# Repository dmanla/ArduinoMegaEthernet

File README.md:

# Arduino-Mega Compatible Secure Connectivity Development Platform

**WARNING**: This project is under development and has not yet been validated.

This is an open hardware platform designed for the development of secure wired-network applications. It is fully compatible with all Arduino Mega-compatible hardware and software.

This project was inspired by (but not a copy of) the Freetronics EtherMega: https://github.com/freetronics/EtherMega
This project was created as an alternative to the platform offered by Freetronics.

Features:
- CH340 USB->Serial Converter (Functionally similar to FT232, Driver should be installed automatically)
- Jumper Configurable IO: Certain pins (D3, D6, D8, D9, D13) can be connected to the headers or to integrated peripheral pins.
- 5V 2A USB-C Input
- 6V - 32V VIN Input 
- MicroSD Card Slot
- 10/100 Ethernet provided over SPI using the W5500
- SE050 EdgeLock Plug and Trust Secure Element to provide security features for connected applications, accessible using I2C
- ISM330DHCX Inertial Measurement Unit, accessible using I2C
- MCP7940N Real Time Clock, accessible using I2C
- Level Shifted I2C: Provides connection points for 3V3 I2C Devices (Extra Header), and 5V I2C Devices (Standard Mega Headers)

## Top Render

## Bottom Render

## Side Render

## Relevant Datasheets

- [CH340N](https://datasheet.lcsc.com/szlcsc/Jiangsu-Qin-Heng-CH340C_C84681.pdf): USB->Serial Bridge
- [AP22805AW5](https://www.diodes.com/assets/Datasheets/AP22804_14.pdf): USB Protection
- [AP63205](https://www.diodes.com/assets/Datasheets/AP63200-AP63201-AP63203-AP63205.pdf): DC-DC Switching Converters
- [W5500](http://wizwiki.net/wiki/lib/exe/fetch.php/products:w5500:w5500_ds_v109e.pdf): SPI->Ethernet Bridge
- [ISM330DHCX](https://www.st.com/resource/en/datasheet/ism330dhcx.pdf): "AI Enabled" Inertial Measurement Unit
- [SE050C2HQ1](https://www.nxp.com/docs/en/data-sheet/SE050-DATASHEET.pdf): Security Coprocessor
- [MCP7940N](http://ww1.microchip.com/downloads/en/DeviceDoc/20005010F.pdf): Real-Time Clock **with** Battery Backup
- [Atmega2560](http://ww1.microchip.com/downloads/en/DeviceDoc/Atmel-2549-8-bit-AVR-Microcontroller-ATmega640-1280-1281-2560-2561_datasheet.pdf): Main Microcontroller

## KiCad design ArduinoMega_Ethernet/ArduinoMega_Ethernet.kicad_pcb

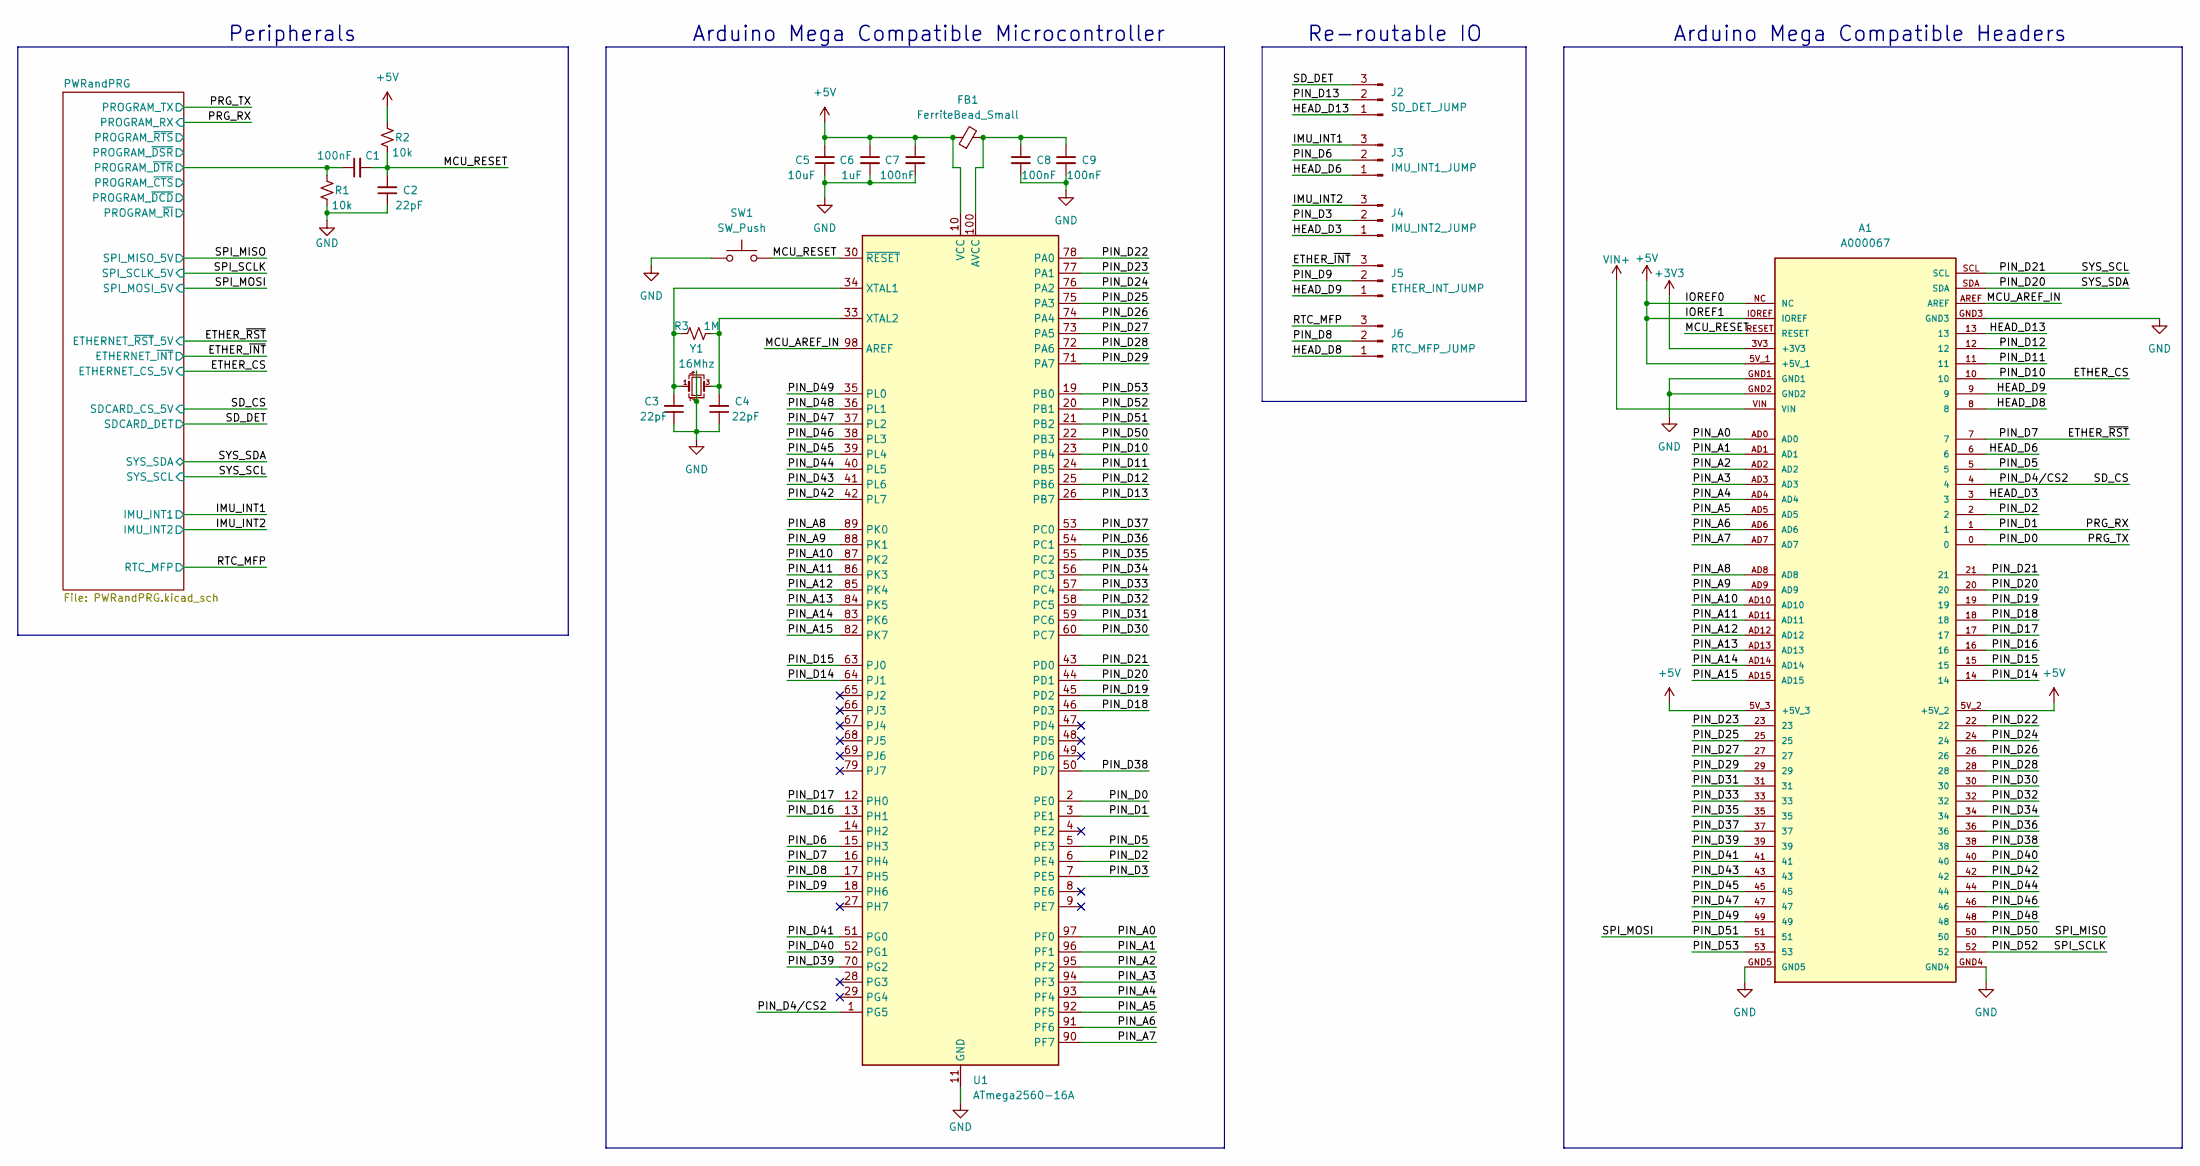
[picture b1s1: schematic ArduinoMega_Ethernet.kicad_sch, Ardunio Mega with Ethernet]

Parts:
A1: A000067; ARDUINO_A000067
C1, C7, C8, C9: 100nF; C_0603_1608Metric
C2, C3, C4: 22pF; C_0603_1608Metric
C5: 10uF; C_0805_2012Metric_Pad1.18x1.45mm_HandSolder
C6: 1uF; C_0603_1608Metric
FB1: FerriteBead_Small; L_0603_1608Metric
J2: SD_DET_JUMP; PinHeader_1x03_P2.54mm_Vertical
J3: IMU_INT1_JUMP; PinHeader_1x03_P2.54mm_Vertical
J4: IMU_INT2_JUMP; PinHeader_1x03_P2.54mm_Vertical
J5: ETHER_INT_JUMP; PinHeader_1x03_P2.54mm_Vertical
J6: RTC_MFP_JUMP; PinHeader_1x03_P2.54mm_Vertical
R1, R2: 10k; R_0603_1608Metric
R3: 1M; R_0603_1608Metric
SW1: SW_Push; SW_Push_SPST_NO_Alps_SKRK
U1: ATmega2560-16A; TQFP-100_14x14mm_P0.5mm
Y1: 16Mhz; Crystal_SMD_3225-4Pin_3.2x2.5mm

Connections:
+3V3: A1.3V3 (+3V3); also elsewhere on the board
+5V: A1.5V_1 (+5V_1), A1.5V_2 (+5V_2), A1.5V_3 (+5V_3), A1.IOREF, A1.NC, C5.2, C6.1, C7.1, FB1.1, R2.1, U1.10 (VCC), U1.31 (VCC), U1.61 (VCC), U1.80 (VCC); also elsewhere on the board
/ETHER_CS: A1.10, U1.23 (PB4); also elsewhere on the board
/ETHER_~INT: J5.3; also elsewhere on the board
/ETHER_~RST: A1.7, U1.16 (PH4); also elsewhere on the board
/HEAD_D3: A1.3, J4.1
/HEAD_D6: A1.6, J3.1
/HEAD_D8: A1.8, J6.1
/HEAD_D9: A1.9, J5.1
/HEAD_D13: A1.13, J2.1
/IMU_INT1: J3.3; also elsewhere on the board
/IMU_INT2: J4.3; also elsewhere on the board
/MCU_AREF_IN: A1.AREF, U1.98 (AREF)
/MCU_RESET: A1.RESET, C1.2, C2.2, R2.2, SW1.2, U1.30 (~RESET)
/PIN_A0: A1.AD0, U1.97 (PF0)
/PIN_A1: A1.AD1, U1.96 (PF1)
/PIN_A2: A1.AD2, U1.95 (PF2)
/PIN_A3: A1.AD3, U1.94 (PF3)
/PIN_A4: A1.AD4, U1.93 (PF4)
/PIN_A5: A1.AD5, U1.92 (PF5)
/PIN_A6: A1.AD6, U1.91 (PF6)
/PIN_A7: A1.AD7, U1.90 (PF7)
/PIN_A8: A1.AD8, U1.89 (PK0)
/PIN_A9: A1.AD9, U1.88 (PK1)
/PIN_A10: A1.AD10, U1.87 (PK2)
/PIN_A11: A1.AD11, U1.86 (PK3)
/PIN_A12: A1.AD12, U1.85 (PK4)
/PIN_A13: A1.AD13, U1.84 (PK5)
/PIN_A14: A1.AD14, U1.83 (PK6)
/PIN_A15: A1.AD15, U1.82 (PK7)
/PIN_D0: A1.0, U1.2 (PE0); also elsewhere on the board
/PIN_D1: A1.1, U1.3 (PE1); also elsewhere on the board
/PIN_D2: A1.2, U1.6 (PE4)
/PIN_D3: J4.2, U1.7 (PE5)
/PIN_D4/CS2: A1.4, U1.1 (PG5); also elsewhere on the board
/PIN_D5: A1.5, U1.5 (PE3)
/PIN_D6: J3.2, U1.15 (PH3)
/PIN_D8: J6.2, U1.17 (PH5)
/PIN_D9: J5.2, U1.18 (PH6)
/PIN_D11: A1.11, U1.24 (PB5)
/PIN_D12: A1.12, U1.25 (PB6)
/PIN_D13: J2.2, U1.26 (PB7)
/PIN_D14: A1.14, U1.64 (PJ1)
/PIN_D15: A1.15, U1.63 (PJ0)
/PIN_D16: A1.16, U1.13 (PH1)
/PIN_D17: A1.17, U1.12 (PH0)
/PIN_D18: A1.18, U1.46 (PD3)
/PIN_D19: A1.19, U1.45 (PD2)
/PIN_D20: A1.20, A1.SDA, U1.44 (PD1); also elsewhere on the board
/PIN_D21: A1.21, A1.SCL, U1.43 (PD0); also elsewhere on the board
/PIN_D22: A1.22, U1.78 (PA0)
/PIN_D23: A1.23, U1.77 (PA1)
/PIN_D24: A1.24, U1.76 (PA2)
/PIN_D25: A1.25, U1.75 (PA3)
/PIN_D26: A1.26, U1.74 (PA4)
/PIN_D27: A1.27, U1.73 (PA5)
/PIN_D28: A1.28, U1.72 (PA6)
/PIN_D29: A1.29, U1.71 (PA7)
/PIN_D30: A1.30, U1.60 (PC7)
/PIN_D31: A1.31, U1.59 (PC6)
/PIN_D32: A1.32, U1.58 (PC5)
/PIN_D33: A1.33, U1.57 (PC4)
/PIN_D34: A1.34, U1.56 (PC3)
/PIN_D35: A1.35, U1.55 (PC2)
/PIN_D36: A1.36, U1.54 (PC1)
/PIN_D37: A1.37, U1.53 (PC0)
/PIN_D38: A1.38, U1.50 (PD7)
/PIN_D39: A1.39, U1.70 (PG2)
/PIN_D40: A1.40, U1.52 (PG1)
/PIN_D41: A1.41, U1.51 (PG0)
/PIN_D42: A1.42, U1.42 (PL7)
/PIN_D43: A1.43, U1.41 (PL6)
/PIN_D44: A1.44, U1.40 (PL5)
/PIN_D45: A1.45, U1.39 (PL4)
/PIN_D46: A1.46, U1.38 (PL3)
/PIN_D47: A1.47, U1.37 (PL2)
/PIN_D48: A1.48, U1.36 (PL1)
/PIN_D49: A1.49, U1.35 (PL0)
/PIN_D50: A1.50, U1.22 (PB3); also elsewhere on the board
/PIN_D51: A1.51, U1.21 (PB2); also elsewhere on the board
/PIN_D52: A1.52, U1.20 (PB1); also elsewhere on the board
/PIN_D53: A1.53, U1.19 (PB0)
/PWRandPRG/PROGRAM_~DTR: C1.1, R1.1; also elsewhere on the board
/RTC_MFP: J6.3; also elsewhere on the board
/SD_DET: J2.3; also elsewhere on the board
GND: A1.GND1, A1.GND2, A1.GND3, A1.GND4, A1.GND5, C2.1, C3.1, C4.1, C5.1, C6.2, C7.2, C8.2, C9.2, R1.2, SW1.1, U1.11 (GND), U1.32 (GND), U1.62 (GND), U1.81 (GND), U1.99 (GND), Y1.2, Y1.4; also elsewhere on the board
unnamed: C8.1, C9.1, FB1.2, U1.100 (AVCC)
unnamed: C3.2, R3.1, U1.34 (XTAL1), Y1.1
unnamed: C4.2, R3.2, U1.33 (XTAL2), Y1.3
VIN+: A1.VIN; also elsewhere on the board

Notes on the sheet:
Peripherals
Arduino Mega Compatible Headers
Re-routable IO
Arduino Mega Compatible Microcontroller

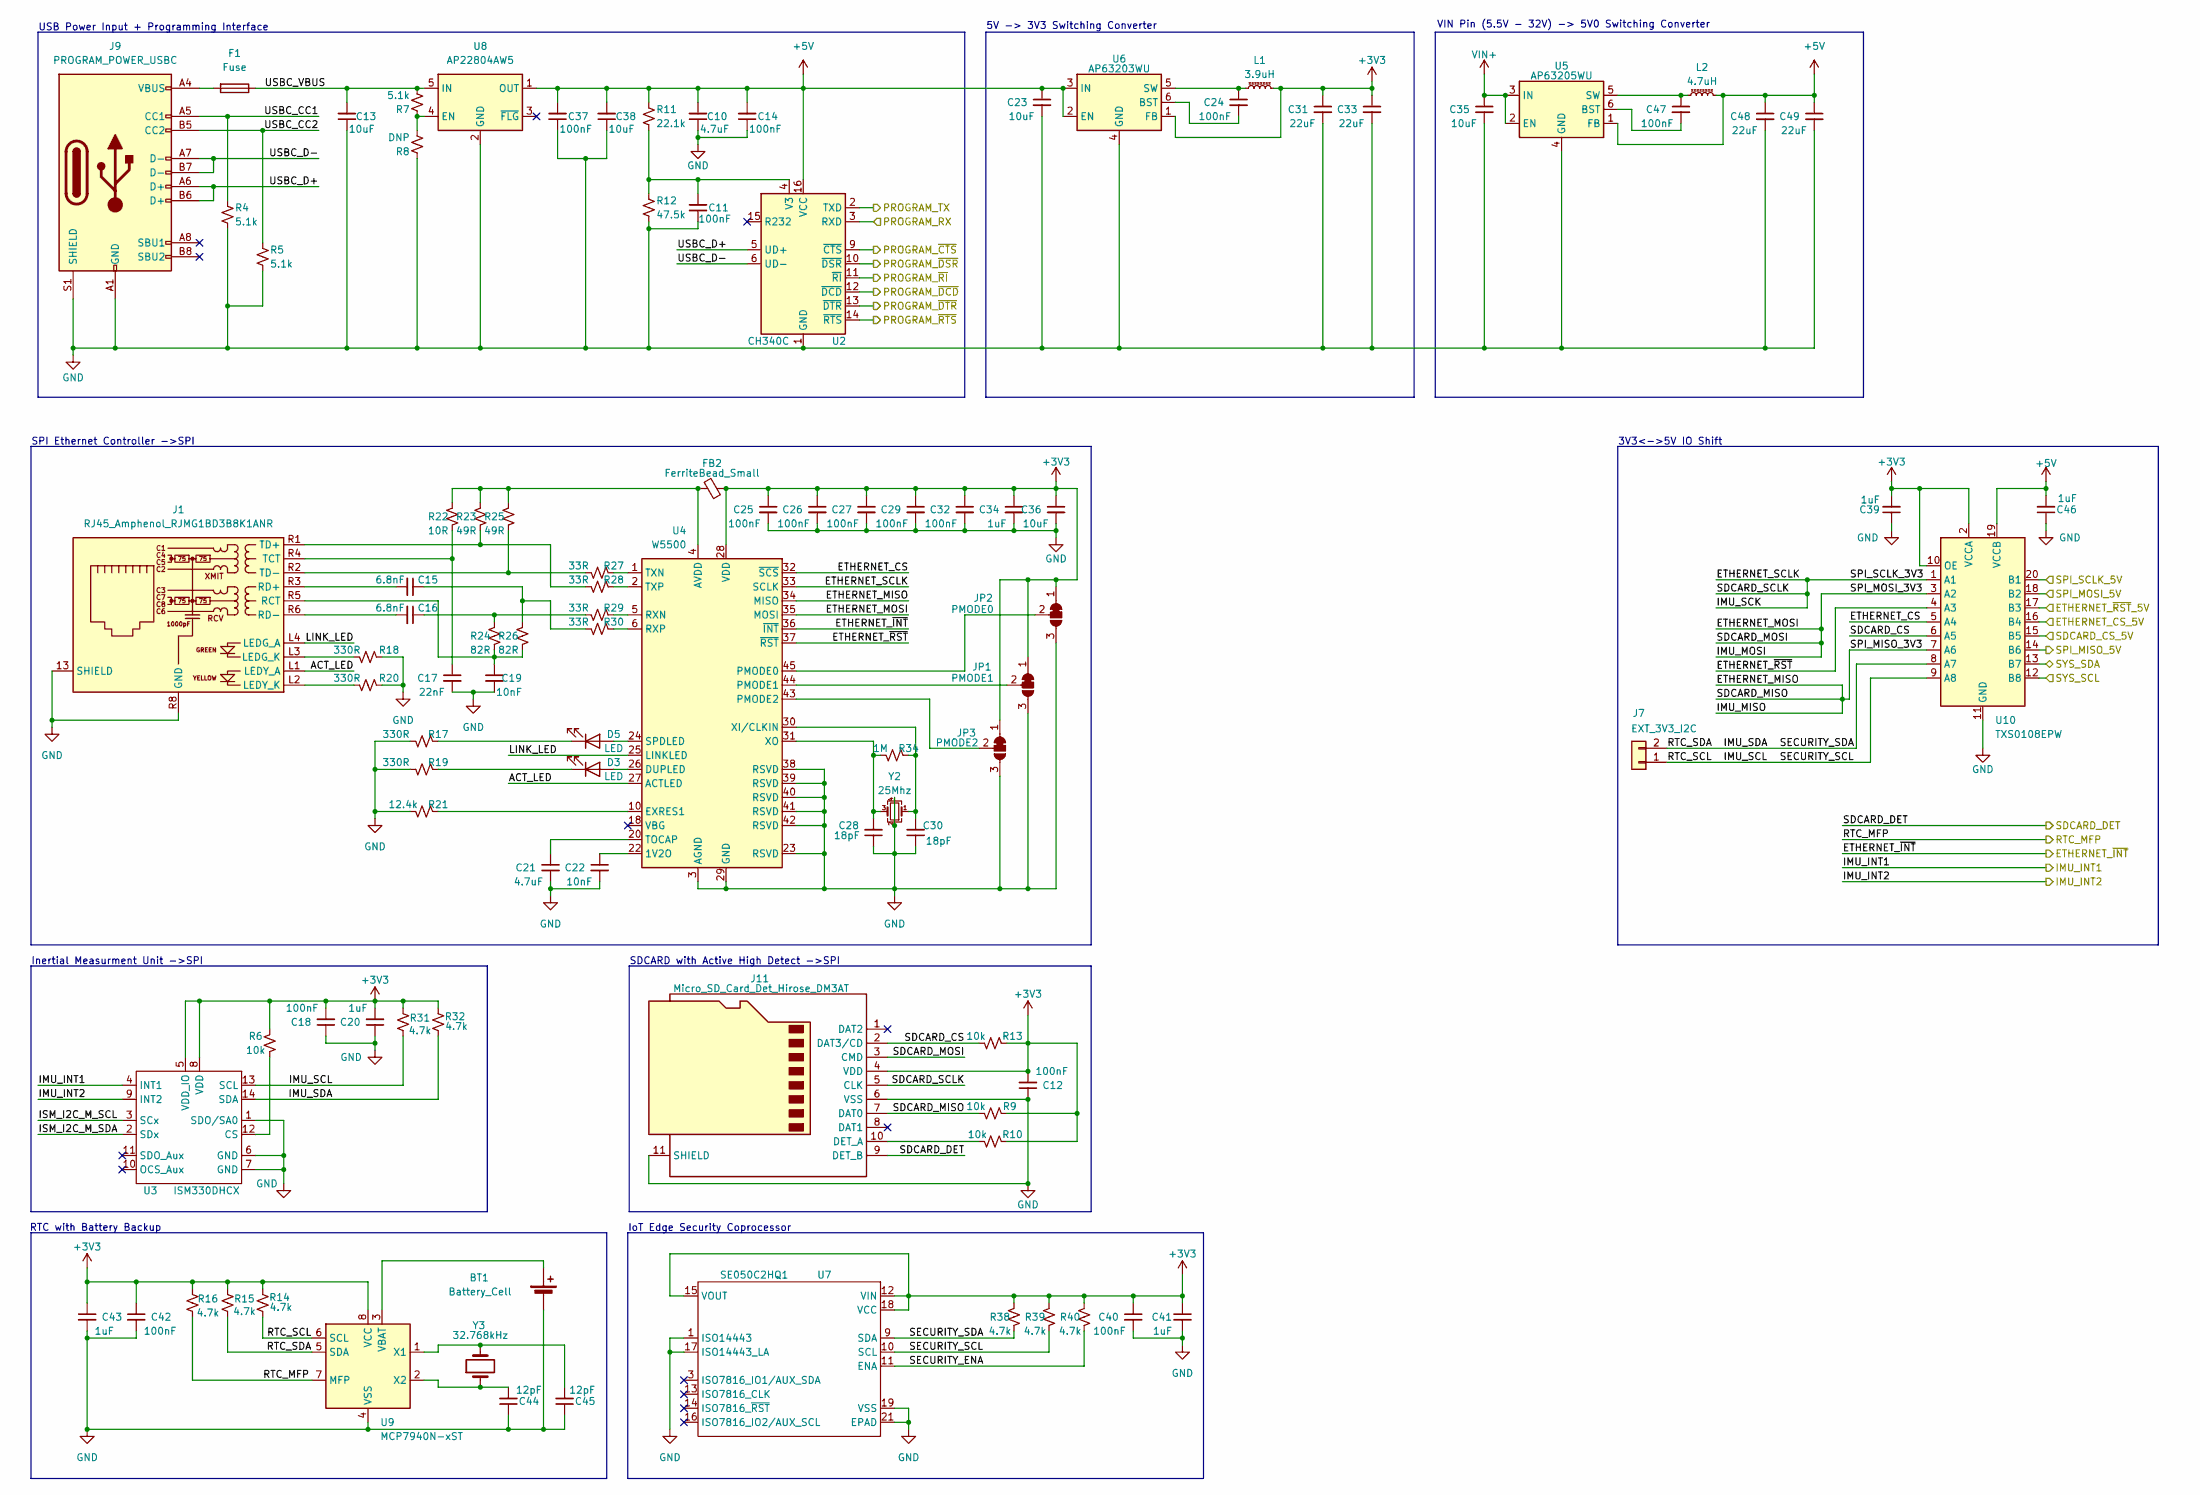
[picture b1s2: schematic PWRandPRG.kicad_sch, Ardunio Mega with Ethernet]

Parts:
BT1: Battery_Cell; JST_PH_B2B-PH-K_1x02_P2.00mm_Vertical
C10, C21: 4.7uF; C_0805_2012Metric_Pad1.18x1.45mm_HandSolder
C11, C12, C14, C18, C24, C25, C26, C27, C29, C32, C37, C40, C42, C47: 100nF; C_0603_1608Metric
C13, C23, C35, C36, C38: 10uF; C_0805_2012Metric_Pad1.18x1.45mm_HandSolder
C15, C16: 6.8nF; C_0603_1608Metric
C17: 22nF; C_0603_1608Metric
C19, C22: 10nF; C_0603_1608Metric
C20, C34, C39, C41, C43, C46: 1uF; C_0603_1608Metric
C28, C30: 18pF; C_0402_1005Metric_Pad0.74x0.62mm_HandSolder
C31, C33, C48, C49: 22uF; C_1210_3225Metric_Pad1.33x2.70mm_HandSolder
C44, C45: 12pF; C_0402_1005Metric_Pad0.74x0.62mm_HandSolder
D3, D5: LED; LED_0603_1608Metric
F1: Fuse; Fuse_1206_3216Metric
FB2: FerriteBead_Small; L_0603_1608Metric
J1: RJ45_Amphenol_RJMG1BD3B8K1ANR
J7: EXT_3V3_I2C; PinHeader_1x02_P2.54mm_Vertical
J9: PROGRAM_POWER_USBC; USB_C_Receptacle_HRO_TYPE-C-31-M-12
J11: Micro_SD_Card_Det_Hirose_DM3AT; microSD_HC_Hirose_DM3AT-SF-PEJM5
JP1: PMODE1; SolderJumper-3_P1.3mm_Bridged12_Pad1.0x1.5mm
JP2: PMODE0; SolderJumper-3_P1.3mm_Bridged12_Pad1.0x1.5mm
JP3: PMODE2; SolderJumper-3_P1.3mm_Bridged12_Pad1.0x1.5mm
L1: 3.9uH; L_APV_ANR6028
L2: 4.7uH; L_APV_ANR6028
R4, R5, R7: 5.1k; R_0603_1608Metric
R6, R9, R10, R13: 10k; R_0603_1608Metric
R8: DNP; R_0603_1608Metric
R11: 22.1k; R_0603_1608Metric
R12: 47.5k; R_0603_1608Metric
R14, R15, R16, R31, R32, R38, R39, R40: 4.7k; R_0603_1608Metric
R17, R18, R19, R20: 330R; R_0603_1608Metric
R21: 12.4k; R_0603_1608Metric
R22: 10R; R_0603_1608Metric
R23, R25: 49R; R_0603_1608Metric
R24, R26: 82R; R_0603_1608Metric
R27, R28, R29, R30: 33R; R_0603_1608Metric
R34: 1M; R_0603_1608Metric
U2: CH340C; SOIC-16_3.9x9.9mm_P1.27mm
U3: ISM330DHCX; LGA-14_3x2.5mm_P0.5mm_LayoutBorder3x4y
U4: W5500; LQFP-48_7x7mm_P0.5mm
U5: AP63205WU; TSOT-23-6
U6: AP63203WU; TSOT-23-6
U7: SE050C2HQ1; QFN-20-1EP_3x3mm_P0.4mm_EP1.65x1.65mm
U8: AP22804AW5; SOT-23-5
U9: MCP7940N-xST; MSOP-8_3x3mm_P0.65mm
U10: TXS0108EPW; TSSOP-20_4.4x6.5mm_P0.65mm
Y2: 25Mhz; Crystal_SMD_3225-4Pin_3.2x2.5mm
Y3: 32.768kHz; Crystal_SMD_EuroQuartz_EQ161-2Pin_3.2x1.5mm_HandSoldering

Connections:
+3V3: C12.2, C18.2, C20.2, C25.1, C26.1, C27.1, C29.1, C31.1, C32.1, C33.1, C34.1, C36.1, C39.2, C40.1, C41.1, C42.1, C43.1, FB2.1, J11.4 (VDD), JP1.1 (A), JP2.1 (A), JP3.1 (A), L1.2, R6.1, R9.1, R10.1, R13.1, R14.1, R15.1, R16.1, R31.1, R32.1, R38.1, R39.1, R40.1, U3.5 (VDD_IO), U3.8 (VDD), U4.28 (VDD), U6.1 (FB), U7.12 (VIN), U7.15 (VOUT), U7.18 (VCC), U9.8 (VCC), U10.2 (VCCA), U10.10 (OE); also elsewhere on the board
+5V: C10.2, C14.2, C23.1, C37.2, C38.2, C46.2, C48.1, C49.1, L2.2, R11.2, U2.16 (VCC), U5.1 (FB), U6.2 (EN), U6.3 (IN), U8.1 (OUT), U10.19 (VCCB); also elsewhere on the board
/ETHER_CS: U10.16 (B4); also elsewhere on the board
/ETHER_~INT: U4.36 (~INT); also elsewhere on the board
/ETHER_~RST: U10.17 (B3); also elsewhere on the board
/IMU_INT1: U3.4 (INT1); also elsewhere on the board
/IMU_INT2: U3.9 (INT2); also elsewhere on the board
/PIN_D0: U2.2 (TXD); also elsewhere on the board
/PIN_D1: U2.3 (RXD); also elsewhere on the board
/PIN_D4/CS2: U10.15 (B5); also elsewhere on the board
/PIN_D20: U10.13 (B7); also elsewhere on the board
/PIN_D21: U10.12 (B8); also elsewhere on the board
/PIN_D50: U10.14 (B6); also elsewhere on the board
/PIN_D51: U10.18 (B2); also elsewhere on the board
/PIN_D52: U10.20 (B1); also elsewhere on the board
/PWRandPRG/ACT_LED: J1.L1 (LEDY_A), U4.27 (ACTLED)
/PWRandPRG/ETHERNET_CS: U4.32 (~SCS), U10.5 (A4)
/PWRandPRG/ETHERNET_MISO: J11.7 (DAT0), R9.2, U4.34 (MISO), U10.7 (A6)
/PWRandPRG/ETHERNET_MOSI: J11.3 (CMD), U4.35 (MOSI), U10.3 (A2)
/PWRandPRG/ETHERNET_SCLK: J11.5 (CLK), U4.33 (SCLK), U10.1 (A1)
/PWRandPRG/ETHERNET_~RST: U4.37 (~RST), U10.4 (A3)
/PWRandPRG/IMU_SCL: J7.1, R14.2, R31.2, R39.2, U3.13 (SCL), U7.10 (SCL), U9.6 (SCL), U10.9 (A8)
/PWRandPRG/IMU_SDA: J7.2, R15.2, R32.2, R38.2, U3.14 (SDA), U7.9 (SDA), U9.5 (SDA), U10.8 (A7)
/PWRandPRG/ISM_I2C_M_SCL: U3.3 (SCx)
/PWRandPRG/ISM_I2C_M_SDA: U3.2 (SDx)
/PWRandPRG/LINK_LED: J1.L4 (LEDG_A), U4.25 (LINKLED)
/PWRandPRG/PROGRAM_~CTS: U2.9 (~CTS)
/PWRandPRG/PROGRAM_~DCD: U2.12 (~DCD)
/PWRandPRG/PROGRAM_~DSR: U2.10 (~DSR)
/PWRandPRG/PROGRAM_~DTR: U2.13 (~DTR); also elsewhere on the board
/PWRandPRG/PROGRAM_~RI: U2.11 (~RI)
/PWRandPRG/PROGRAM_~RTS: U2.14 (~RTS)
/PWRandPRG/SDCARD_CS: J11.2 (DAT3/CD), R13.2, U10.6 (A5)
/PWRandPRG/SECURITY_ENA: R40.2, U7.11 (ENA)
/PWRandPRG/USBC_CC1: J9.A5 (CC1), R4.2
/PWRandPRG/USBC_CC2: J9.B5 (CC2), R5.2
/PWRandPRG/USBC_D+: J9.A6 (D+), J9.B6 (D+), U2.5 (UD+)
/PWRandPRG/USBC_D-: J9.A7 (D-), J9.B7 (D-), U2.6 (UD-)
/PWRandPRG/USBC_VBUS: C13.2, F1.1, R7.1, U8.5 (IN)
/RTC_MFP: R16.2, U9.7 (MFP); also elsewhere on the board
/SD_DET: J11.9 (DET_B); also elsewhere on the board
GND: BT1.2 (-), C10.1, C11.1, C12.1, C13.1, C14.1, C17.2, C18.1, C19.2, C20.1, C21.2, C22.2, C23.2, C25.2, C26.2, C27.2, C28.1, C29.2, C30.1, C31.2, C32.2, C33.2, C34.2, C35.2, C36.2, C37.1, C38.1, C39.1, C40.2, C41.2, C42.2, C43.2, C44.1, C45.1, C46.1, C48.2, C49.2, J1.13 (SHIELD), J1.R8 (GND), J9.A1 (GND), J9.A12 (GND), J9.B1 (GND), J9.B12 (GND), J9.S1 (SHIELD), J11.6 (VSS), J11.11 (SHIELD), JP1.3 (B), JP2.3 (B), JP3.3 (B), R4.1, R5.1, R8.2, R12.1, R17.2, R18.1, R19.2, R20.1, R21.2, U2.1 (GND), U3.1 (SDO/SA0), U3.6 (GND), U3.7 (GND), U4.3 (AGND), U4.9 (AGND), U4.14 (AGND), U4.16 (AGND), U4.19 (AGND), U4.23 (RSVD), U4.29 (GND), U4.38 (RSVD), U4.39 (RSVD), U4.40 (RSVD), U4.41 (RSVD), U4.42 (RSVD), U4.48 (AGND), U5.4 (GND), U6.4 (GND), U7.1 (ISO14443), U7.17 (ISO14443_LA), U7.19 (VSS), U7.21 (EPAD), U8.2 (GND), U9.4 (VSS), U10.11 (GND), Y2.2, Y2.4; also elsewhere on the board
unnamed: BT1.1 (+), U9.3 (VBAT)
unnamed: C15.1, R26.1, R30.2
unnamed: C16.1, R24.1, R29.2
unnamed: D3.2 (A), U4.26 (DUPLED)
unnamed: D3.1 (K), R19.1
unnamed: D5.2 (A), U4.24 (SPDLED)
unnamed: D5.1 (K), R17.1
unnamed: F1.2, J9.A4 (VBUS), J9.A9 (VBUS), J9.B4 (VBUS), J9.B9 (VBUS)
unnamed: FB2.2, R22.1, R23.1, R25.1, U4.4 (AVDD), U4.8 (AVDD), U4.11 (AVDD), U4.15 (AVDD), U4.17 (AVDD), U4.21 (AVDD)
unnamed: J1.L3 (LEDG_K), R18.2
unnamed: J1.L2 (LEDY_K), R20.2
unnamed: C19.1, J1.R5 (RCT), R24.2, R26.2
unnamed: C15.2, J1.R3 (RD+)
unnamed: C16.2, J1.R6 (RD-)
unnamed: C17.1, J1.R4 (TCT), R22.2
unnamed: J1.R1 (TD+), R23.2, R28.2
unnamed: J1.R2 (TD-), R25.2, R27.2
unnamed: J11.10 (DET_A), R10.2
unnamed: JP1.2 (C), U4.44 (PMODE1)
unnamed: JP2.2 (C), U4.45 (PMODE0)
unnamed: JP3.2 (C), U4.43 (PMODE2)
unnamed: C11.2, R11.1, R12.2, U2.4 (V3)
unnamed: R6.2, U3.12 (CS)
unnamed: C22.1, U4.22 (1V2O)
unnamed: R21.1, U4.10 (EXRES1)
unnamed: R29.1, U4.5 (RXN)
unnamed: R30.1, U4.6 (RXP)
unnamed: C21.1, U4.20 (TOCAP)
unnamed: R27.1, U4.1 (TXN)
unnamed: R28.1, U4.2 (TXP)
unnamed: C30.2, R34.1, U4.30 (XI/CLKIN), Y2.1
unnamed: C28.2, R34.2, U4.31 (XO), Y2.3
unnamed: C47.2, U5.6 (BST)
unnamed: C47.1, L2.1, U5.5 (SW)
unnamed: C24.2, U6.6 (BST)
unnamed: C24.1, L1.1, U6.5 (SW)
unnamed: R7.2, R8.1, U8.4 (EN)
unnamed: C45.2, U9.1 (X1), Y3.2
unnamed: C44.2, U9.2 (X2), Y3.1
VIN+: C35.1, U5.2 (EN), U5.3 (IN); also elsewhere on the board

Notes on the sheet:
SPI Ethernet Controller ->SPI
3V3<->5V IO Shift
USB Power Input + Programming Interface
IoT Edge Security Coprocessor
VIN Pin (5.5V - 32V) -> 5V0 Switching Converter
SDCARD with Active High Detect ->SPI
5V -> 3V3 Switching Converter
RTC with Battery Backup
Inertial Measurment Unit ->SPI

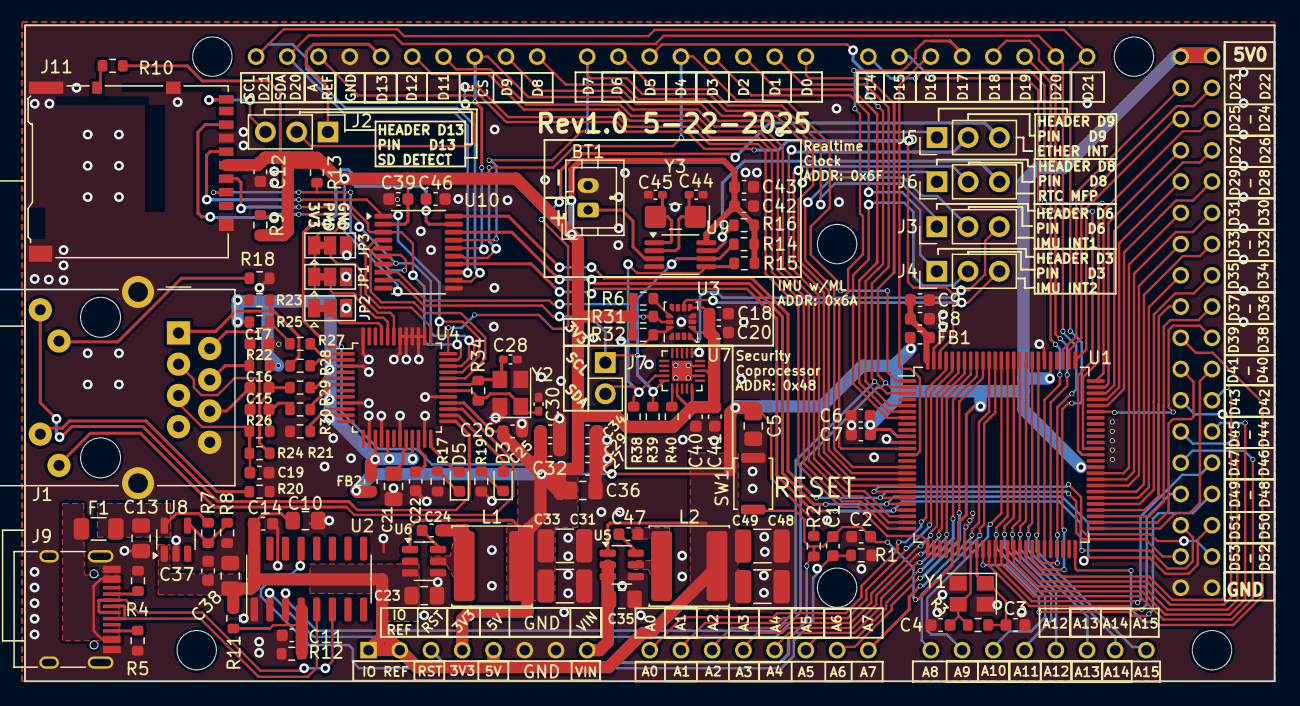
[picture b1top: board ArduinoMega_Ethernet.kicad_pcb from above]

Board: 2 copper layers, 101.6 x 53.3 mm, 120 parts (0 on the bottom side), 145 nets.

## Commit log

2025-05-17 renders
2025-05-17 update renders
2025-05-17 link images to readme
2025-05-17 ch340 note
2025-05-17 remove old schematic
2025-05-18 add usb protection, fix ioref
2025-05-18 datasheet links
2025-05-18 fix datasheet links
2025-05-18 Fix IMU I2C, add SD Detect, Fix IoT CoPro Power
2025-05-18 update with imu and copro changes
2025-05-18 schematic with toggle io and rtc
2025-05-18 Update README.md with rtc info
2025-05-18 Update description for clarity
2025-05-19 configurable io jumpers
    configurable io jumpers
2025-05-19 note configurable pins
2025-05-19 remove highlight
2025-05-19 update pos
2025-05-20 I2C and Silkscreen revision
2025-05-20 level shift i2c note
2025-05-20 update title
2025-05-21 update level shifter, configurable pmode
2025-05-21 update capacitor footprints
2025-05-21 Add files via upload
    fix undersized capacitors
2025-05-22 fix VIN pin
2025-05-22 vin note
2025-05-23 finished BOM and component sizing
2025-05-23 swap sd card mosi miso
